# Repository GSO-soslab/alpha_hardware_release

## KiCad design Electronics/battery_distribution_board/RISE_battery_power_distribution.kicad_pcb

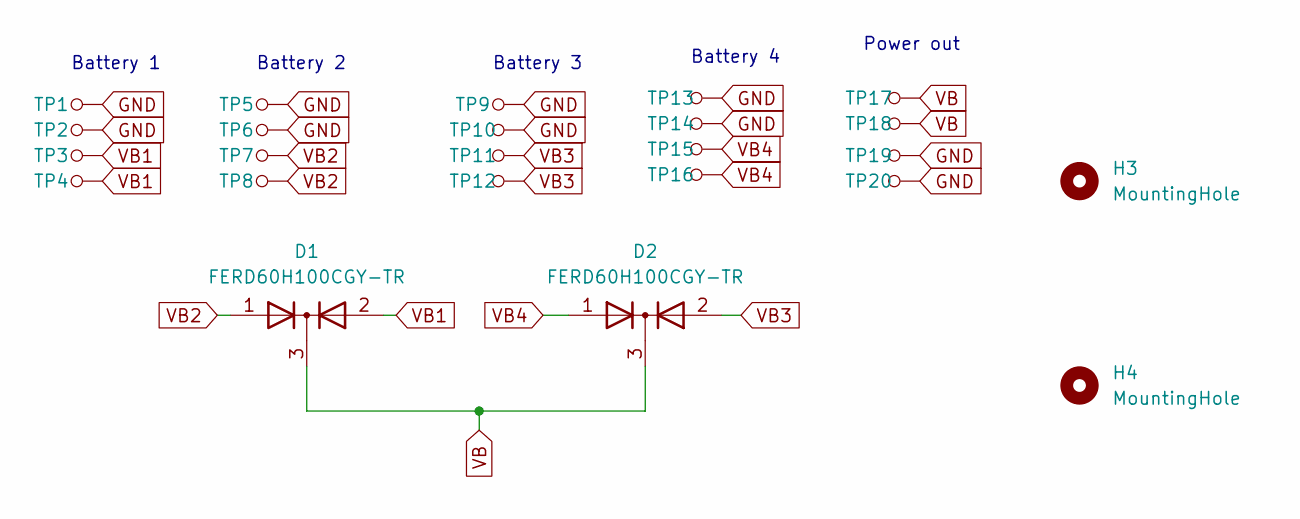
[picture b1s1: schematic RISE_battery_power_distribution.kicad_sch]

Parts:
D1, D2: FERD60H100CGY-TR; STPS41L60CG-TR
H3, H4: MountingHole; MountingHole_2.2mm_M2
TP1, TP2, TP3, TP4, TP5, TP6, TP7, TP8, TP9, TP10, TP11, TP12, TP13, TP14, TP15, TP16, TP17, TP18, TP19, TP20: 5016; Test_Point_3.43x1.78mm; MPN 5016; Digi-Key_PN 36-5016CT-ND

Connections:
GND: TP1.1, TP2.1, TP5.1, TP6.1, TP9.1, TP10.1, TP13.1, TP14.1, TP19.1, TP20.1
VB: D1.3 (K), D2.3 (K), TP17.1, TP18.1
VB1: D1.2 (A), TP3.1, TP4.1
VB2: D1.1 (A), TP7.1, TP8.1
VB3: D2.2 (A), TP11.1, TP12.1
VB4: D2.1 (A), TP15.1, TP16.1

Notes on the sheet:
Battery 3
Battery 2
Battery 1
Battery 4
Power out

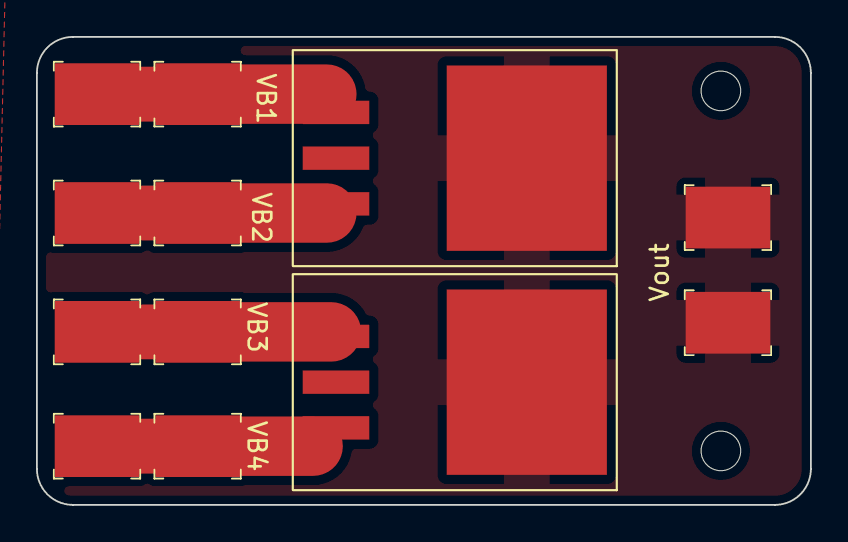
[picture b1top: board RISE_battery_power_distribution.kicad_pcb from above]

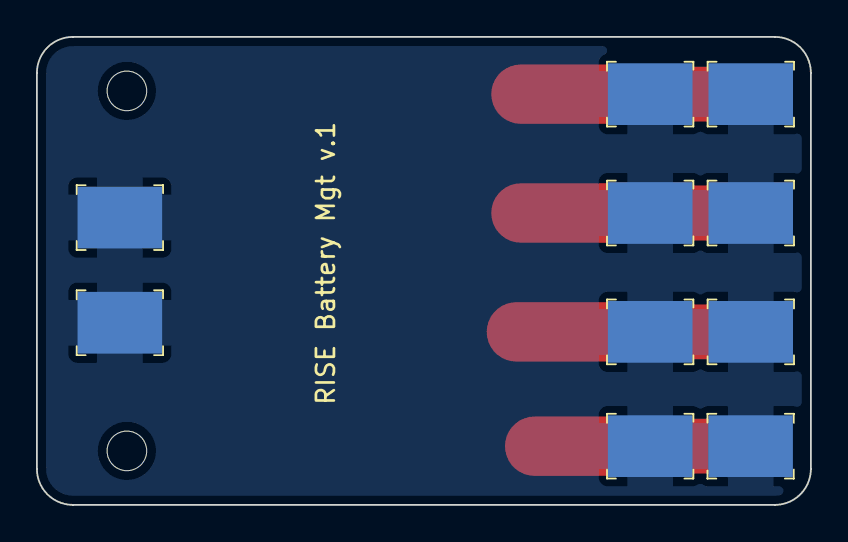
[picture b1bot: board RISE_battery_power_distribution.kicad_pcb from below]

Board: 2 copper layers, 43.0 x 26.0 mm, 24 parts (10 on the bottom side), 6 nets.

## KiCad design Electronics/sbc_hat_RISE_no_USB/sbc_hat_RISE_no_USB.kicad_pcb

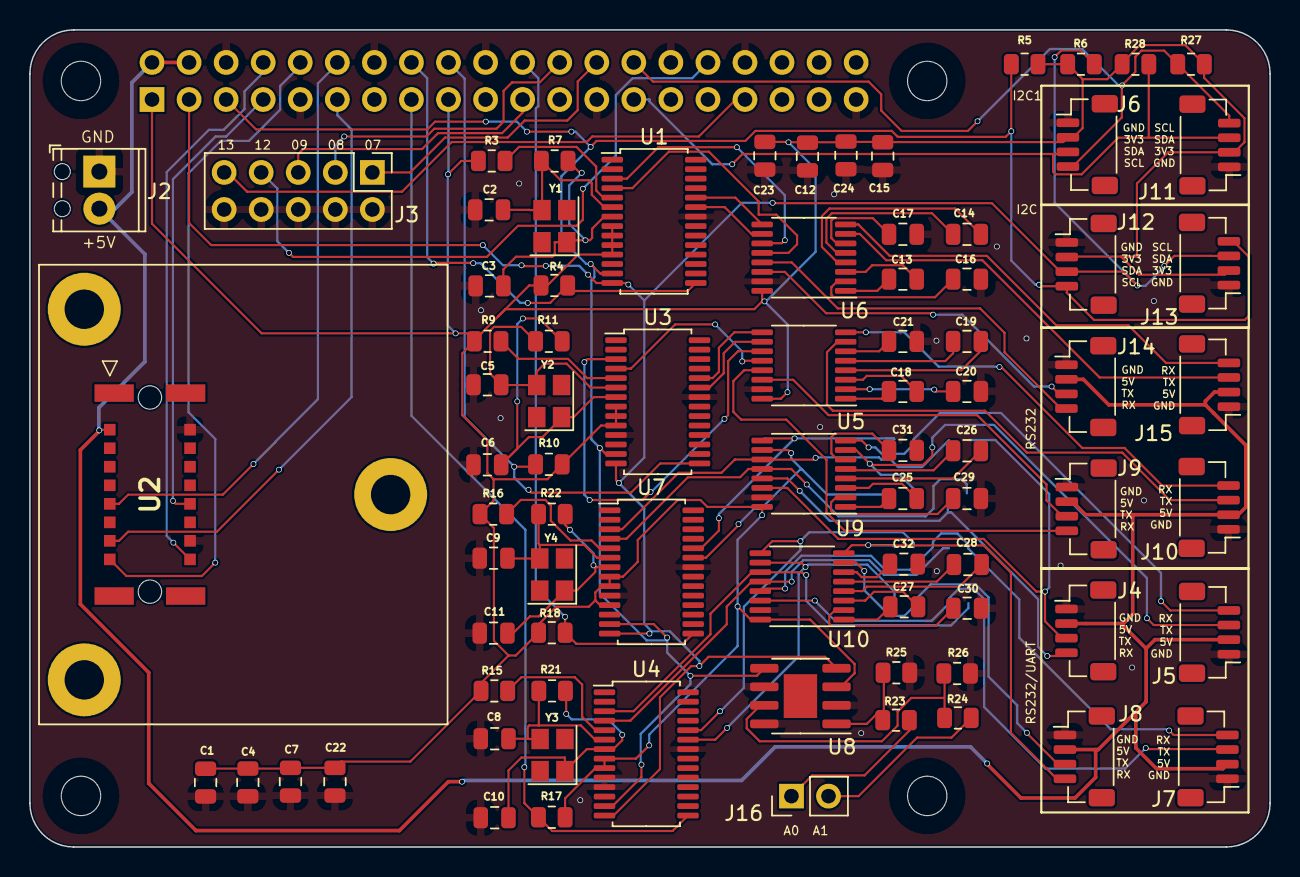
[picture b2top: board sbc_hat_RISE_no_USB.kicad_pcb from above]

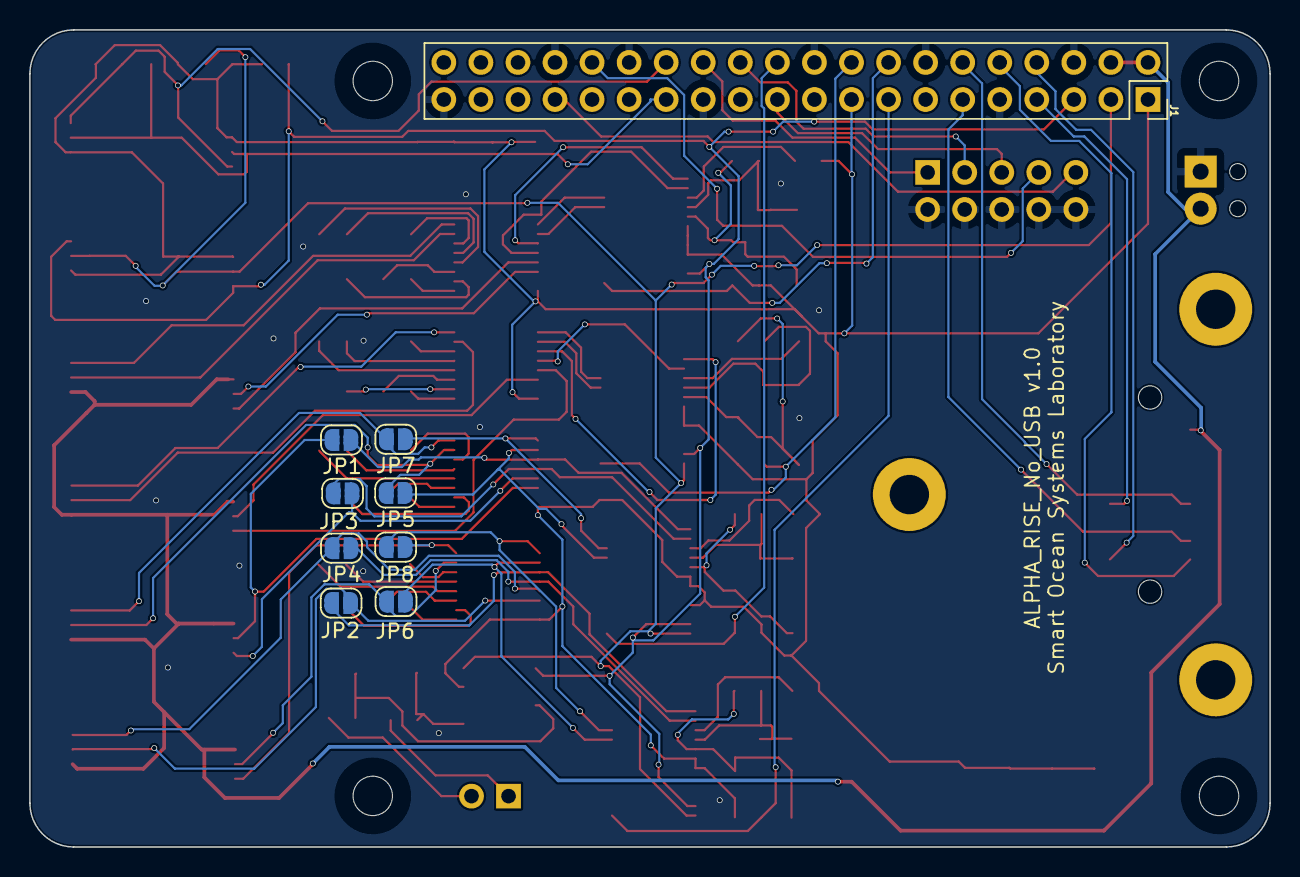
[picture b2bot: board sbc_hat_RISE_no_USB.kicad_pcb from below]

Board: 2 copper layers, 85.0 x 56.0 mm, 94 parts (9 on the bottom side), 93 nets.

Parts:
C1, C4, C7, C12, C13, C14, C15, C16, C17, C18, C19, C20, C21, C22, C23, C24, C25, C26, C27, C28, C29, C30, C31, C32: 0.1uF; C_0805_2012Metric
C2, C5, C8, C9: 22pF; C_0805_2012Metric
C3, C6, C10, C11: 33pF; C_0805_2012Metric
J1: OX40HAT; PinSocket_2x20_P2.54mm_Vertical
J2: Screw_Terminal_01x02; TerminalBlock_Phoenix_MPT-0,5-2-2.54_1x02_P2.54mm_Horizontal
J3: Conn_02x05_Odd_Even; PinHeader_2x05_P2.54mm_Vertical
J4, J7, J14: RS232-1; JST_SH_BM04B-SRSS-TB_1x04-1MP_P1.00mm_Vertical
J5, J8, J15: RS232-2; JST_SH_BM04B-SRSS-TB_1x04-1MP_P1.00mm_Vertical
J6, J11: I2C-3; JST_SH_BM04B-SRSS-TB_1x04-1MP_P1.00mm_Vertical
J9: RS485-1; JST_SH_BM04B-SRSS-TB_1x04-1MP_P1.00mm_Vertical
J10: RS485-2; JST_SH_BM04B-SRSS-TB_1x04-1MP_P1.00mm_Vertical
J12: I2C-1; JST_SH_BM04B-SRSS-TB_1x04-1MP_P1.00mm_Vertical
J13: I2C-2; JST_SH_BM04B-SRSS-TB_1x04-1MP_P1.00mm_Vertical
J16: Conn_01x02_Male; PinHeader_1x02_P2.54mm_Vertical
JP1, JP2, JP3, JP4, JP5, JP6, JP7, JP8: SolderJumper_2_Open; SolderJumper-2_P1.3mm_Open_RoundedPad1.0x1.5mm
MH1, MH2, MH3, MH4: MountingHole_2.7mm_M2.5
R3, R4, R9, R10, R15, R16, R17, R18: 1k; R_0805_2012Metric
R5, R6, R27, R28: 4.7k; R_0805_2012Metric
R7, R11, R21, R22: 1M; R_0805_2012Metric
R23, R24: 100k; R_0805_2012Metric
R25, R26: 10K; R_0805_2012Metric
U1, U3, U4, U7: SC16IS752IPW; TSSOP-28_4.4x9.7mm_P0.65mm
U2: MTi630
U5, U6, U9, U10: MAX3232IPWR; TSSOP-16_4.4x5mm_P0.65mm
U8: MCP3422; SOIC-8-1EP_3.9x4.9mm_P1.27mm_EP2.29x3mm
Y1, Y2, Y3, Y4: 14.7456M; Crystal_SMD_3225-4Pin_3.2x2.5mm

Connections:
5V: J1.2 (P5V), J1.4 (P5V), J2.2, J4.2, J5.2, J7.2, J8.2, J9.2, J10.2, J14.2, J15.2, U2.1 (VIN)
A0: R23.2, R25.1, U8.1 (CH1+)
A1: R24.2, R26.1, U8.7 (CH2+)
GND: C1.2, C2.1, C3.1, C4.2, C5.1, C6.1, C7.2, C8.1, C9.1, C10.1, C11.1, C12.1, C15.1, C16.2, C17.2, C20.2, C21.2, C22.2, C23.1, C24.1, C29.2, C30.2, C31.2, C32.2, J1.6 (GND), J1.9 (GND), J1.14 (GND), J1.20 (GND), J1.25 (GND), J1.30 (GND), J1.34 (GND), J1.39 (GND), J2.1, J3.2, J3.4, J3.6, J3.8, J3.10, J4.1, J5.1, J6.1, J7.1, J8.1, J9.1, J10.1, J11.1, J12.1, J13.1, J14.1, J15.1, R25.2, R26.2, U1.22 (VSS), U2.2 (GND), U2.14 (GND), U3.11 (A1/SI), U3.22 (VSS), U4.10 (A0/~CS), U4.11 (A1/SI), U4.22 (VSS), U5.15 (GND), U6.15 (GND), U7.10 (A0/~CS), U7.22 (VSS), U8.2 (CH1-), U8.6 (Vss), U8.8 (CH2-), U9.15 (GND), U10.15 (GND)
GPIO7: J1.26 (BCM7), J3.1
GPIO8: J1.24 (BCM8), J3.3
GPIO9: J1.21 (BCM9), J3.5
GPIO12: J1.32 (BCM12), J3.7
GPIO13: J1.33 (BCM13), J3.9
I2C1_SCL: J1.28 (BCM1), J6.4, J11.4, R27.1
I2C1_SDA: J1.27 (BCM0), J6.3, J11.3, R28.1
I2C_SCL: J1.5 (BCM3), J12.4, J13.4, R5.1, U1.13 (SCL/SCLK), U3.13 (SCL/SCLK), U4.13 (SCL/SCLK), U7.13 (SCL/SCLK), U8.5 (SCL)
I2C_SDA: J1.3 (BCM2), J12.3, J13.3, R6.1, U1.14 (SDA/VSS), U3.14 (SDA/VSS), U4.14 (SDA/VSS), U7.14 (SDA/VSS), U8.4 (SDA)
unnamed: C2.2, R7.1, U1.6 (XTAL1), Y1.3
unnamed: C3.2, R7.2, U1.7 (XTAL2), Y1.1
unnamed: C5.2, R11.1, U3.6 (XTAL1), Y2.3
unnamed: C6.2, R11.2, U3.7 (XTAL2), Y2.1
unnamed: C8.2, R21.1, U4.6 (XTAL1), Y3.3
unnamed: C9.2, R22.1, U7.6 (XTAL1), Y4.3
unnamed: C10.2, R21.2, U4.7 (XTAL2), Y3.1
unnamed: C11.2, R22.2, U7.7 (XTAL2), Y4.1
unnamed: C13.1, U6.3 (C1-)
unnamed: C13.2, U6.1 (C1+)
unnamed: C14.1, U6.5 (C2-)
unnamed: C14.2, U6.4 (C2+)
unnamed: C16.1, U6.2 (VS+)
unnamed: C17.1, U6.6 (VS-)
unnamed: C18.1, U5.3 (C1-)
unnamed: C18.2, U5.1 (C1+)
unnamed: C19.1, U5.5 (C2-)
unnamed: C19.2, U5.4 (C2+)
unnamed: C20.1, U5.2 (VS+)
unnamed: C21.1, U5.6 (VS-)
unnamed: C25.1, U9.3 (C1-)
unnamed: C25.2, U9.1 (C1+)
unnamed: C26.1, U9.5 (C2-)
unnamed: C26.2, U9.4 (C2+)
unnamed: C27.1, U10.3 (C1-)
unnamed: C27.2, U10.1 (C1+)
unnamed: C28.1, U10.5 (C2-)
unnamed: C28.2, U10.4 (C2+)
unnamed: C29.1, U9.2 (VS+)
unnamed: C30.1, U10.2 (VS+)
unnamed: C31.1, U9.6 (VS-)
unnamed: C32.1, U10.6 (VS-)
unnamed: R3.2, U1.5 (~RESET)
unnamed: R9.2, U3.5 (~RESET)
unnamed: R15.2, U4.5 (~RESET)
unnamed: R16.2, U7.5 (~RESET)
PPS_IN: J1.7 (BCM4), U2.10 (SYNC_IN2)
PWM0: J1.12 (BCM18), U2.9 (SYNC_IN1)
RS232_RX1: J14.4, U6.13 (R1IN)
RS232_RX2: J15.4, U6.8 (R2IN)
RS232_RX3: J9.4, U5.13 (R1IN)
RS232_RX4: J10.4, U5.8 (R2IN)
RS232_RX5: J4.4, JP3.2 (B), U9.13 (R1IN)
RS232_RX6: J5.4, JP7.2 (B), U9.8 (R2IN)
RS232_RX7: J7.4, JP4.2 (B), U10.13 (R1IN)
RS232_RX8: J8.4, JP8.2 (B), U10.8 (R2IN)
RS232_TX1: J14.3, U6.14 (T1OUT)
RS232_TX2: J15.3, U6.7 (T2OUT)
RS232_TX3: J9.3, U5.14 (T1OUT)
RS232_TX4: J10.3, U5.7 (T2OUT)
RS232_TX5: J4.3, JP1.2 (B), U9.14 (T1OUT)
RS232_TX6: J5.3, JP5.2 (B), U9.7 (T2OUT)
RS232_TX7: J7.3, JP2.2 (B), U10.14 (T1OUT)
RS232_TX8: J8.3, JP6.2 (B), U10.7 (T2OUT)
SBC_3V3: C1.1, C4.1, C7.1, C12.2, C15.2, C22.1, C23.2, C24.2, J1.1 (P3V3), J1.17 (P3V3), J6.2, J11.2, J12.2, J13.2, R3.1, R4.2, R5.2, R6.2, R9.1, R10.2, R15.1, R16.1, R17.2, R18.2, R27.2, R28.2, U1.8 (VDD), U1.9 (I2C/~SPI), U1.10 (A0/~CS), U1.11 (A1/SI), U3.8 (VDD), U3.9 (I2C/~SPI), U3.10 (A0/~CS), U4.8 (VDD), U4.9 (I2C/~SPI), U5.16 (VCC), U6.16 (VCC), U7.8 (VDD), U7.9 (I2C/~SPI), U7.11 (A1/SI), U8.3 (Vdd), U9.16 (VCC), U10.16 (VCC)
SERIAL_IRQ1: J1.16 (BCM23), R4.1, U1.15 (~IRQ)
SERIAL_IRQ2: J1.18 (BCM24), R10.1, U3.15 (~IRQ)
SERIAL_IRQ3: J1.22 (BCM25), R18.1, U7.15 (~IRQ)
SERIAL_IRQ4: J1.15 (BCM22), R17.1, U4.15 (~IRQ)
SYNC_OUT: J1.11 (BCM17), U2.13 (SYNC_OUT)
UART_RX0: J1.10 (BCM15), U2.15 (UART_TxD)
UART_RX1: U1.4 (RXA), U6.12 (R1OUT)
UART_RX2: U1.24 (RXB), U6.9 (R2OUT)
UART_RX3: U3.4 (RXA), U5.12 (R1OUT)
UART_RX4: U3.24 (RXB), U5.9 (R2OUT)
UART_RX5: JP3.1 (A), U7.4 (RXA), U9.12 (R1OUT)
UART_RX6: JP7.1 (A), U7.24 (RXB), U9.9 (R2OUT)
UART_RX7: JP4.1 (A), U4.4 (RXA), U10.12 (R1OUT)
UART_RX8: JP8.1 (A), U4.24 (RXB), U10.9 (R2OUT)
UART_TX0: J1.8 (BCM14), U2.16 (UART_RxD)
UART_TX1: U1.3 (TXA), U6.11 (T1IN)
UART_TX2: U1.23 (TXB), U6.10 (T2IN)
UART_TX3: U3.3 (TXA), U5.11 (T1IN)
UART_TX4: U3.23 (TXB), U5.10 (T2IN)
UART_TX5: JP1.1 (A), U7.3 (TXA), U9.11 (T1IN)
UART_TX6: JP5.1 (A), U7.23 (TXB), U9.10 (T2IN)
UART_TX7: JP2.1 (A), U4.3 (TXA), U10.11 (T1IN)
UART_TX8: JP6.1 (A), U4.23 (TXB), U10.10 (T2IN)
VB: J16.1, R23.1
VB2: J16.2, R24.1
